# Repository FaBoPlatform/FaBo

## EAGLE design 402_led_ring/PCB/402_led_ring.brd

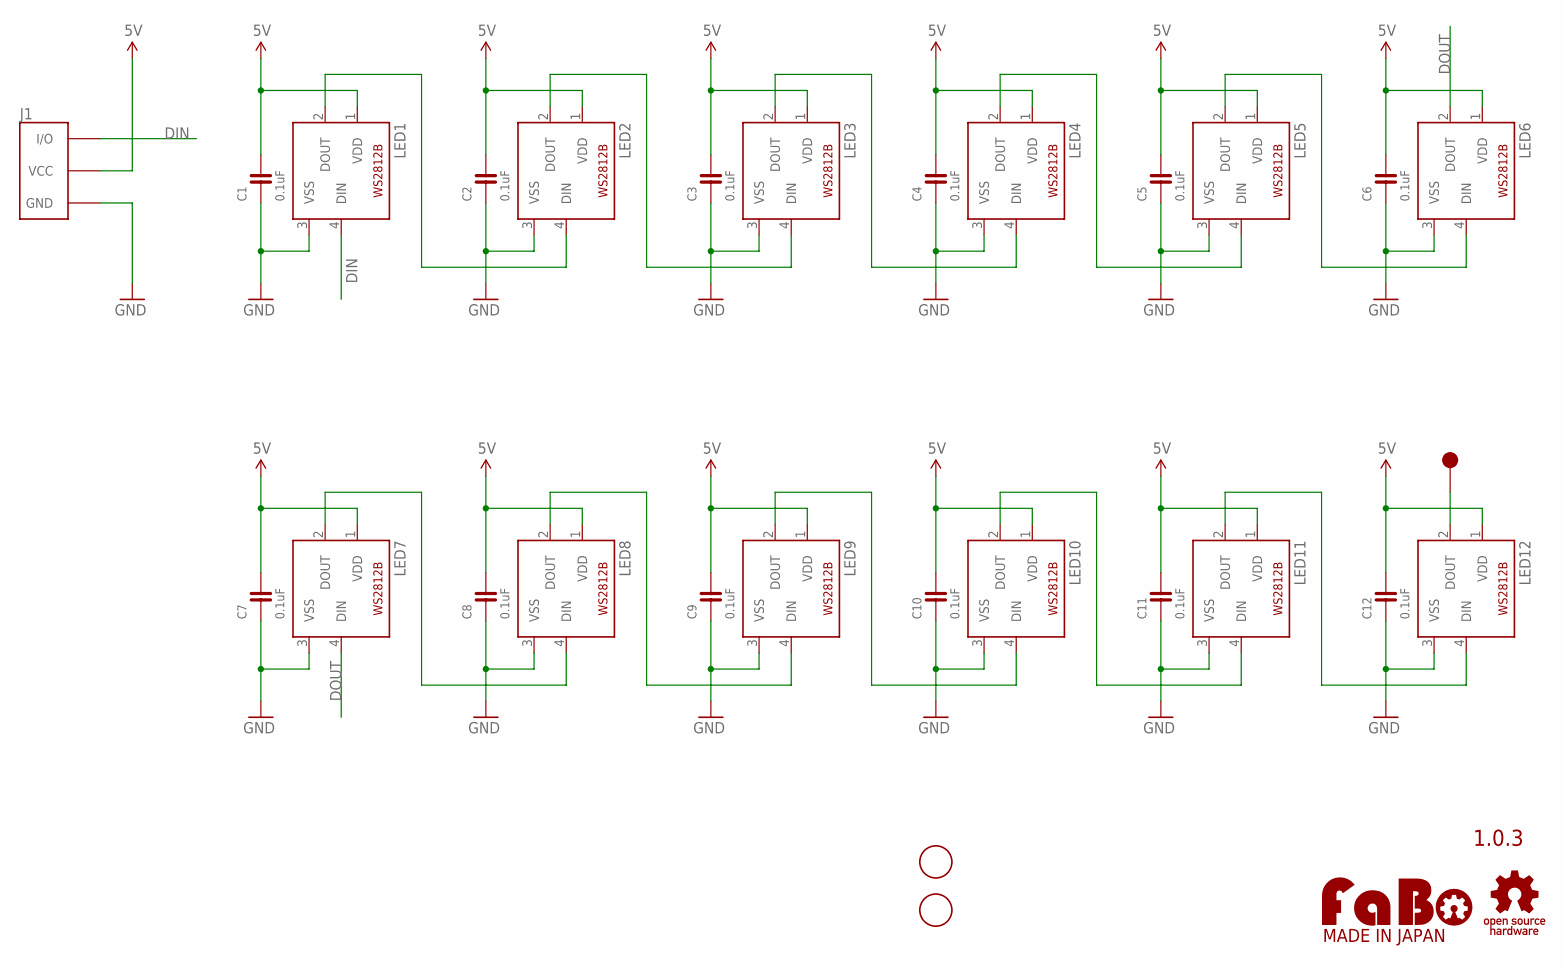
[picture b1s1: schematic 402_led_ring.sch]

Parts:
C1, C2, C3, C4, C5, C6, C7, C8, C9, C10, C11, C12: 0.1uF; 0603
J1: FABO_BRICK_3PIN-S03B-PASK-2_LONG; FABO_BRICK_3PIN_S03B-PASK-2_LONG
LED1, LED2, LED3, LED4, LED5, LED6, LED7, LED8, LED9, LED10, LED11, LED12: WS2812B
TP1: TP-10
U$2, U$3: SCREW-PAD-3MM; SCREWPAD_3MM
U$4: LOGO_OSHW-M_BOTTOM; LOGO_OSHW_M_BOTTOM
U$5: LOGO_FABO-M; LOGO_FABO_MS

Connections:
5V: C1.2, C2.2, C3.2, C4.2, C5.2, C6.2, C7.2, C8.2, C9.2, C10.2, C11.2, C12.2, J1.VCC, LED1.1 (VDD), LED2.1 (VDD), LED3.1 (VDD), LED4.1 (VDD), LED5.1 (VDD), LED6.1 (VDD), LED7.1 (VDD), LED8.1 (VDD), LED9.1 (VDD), LED10.1 (VDD), LED11.1 (VDD), LED12.1 (VDD)
DIN: J1.I/O, LED1.4 (DIN)
DOUT: LED6.2 (DOUT), LED7.4 (DIN)
GND: C1.1, C2.1, C3.1, C4.1, C5.1, C6.1, C7.1, C8.1, C9.1, C10.1, C11.1, C12.1, J1.GND, LED1.3 (VSS), LED2.3 (VSS), LED3.3 (VSS), LED4.3 (VSS), LED5.3 (VSS), LED6.3 (VSS), LED7.3 (VSS), LED8.3 (VSS), LED9.3 (VSS), LED10.3 (VSS), LED11.3 (VSS), LED12.3 (VSS)
unnamed: LED1.2 (DOUT), LED2.4 (DIN)
unnamed: LED2.2 (DOUT), LED3.4 (DIN)
unnamed: LED3.2 (DOUT), LED4.4 (DIN)
unnamed: LED4.2 (DOUT), LED5.4 (DIN)
unnamed: LED5.2 (DOUT), LED6.4 (DIN)
unnamed: LED7.2 (DOUT), LED8.4 (DIN)
unnamed: LED8.2 (DOUT), LED9.4 (DIN)
unnamed: LED9.2 (DOUT), LED10.4 (DIN)
unnamed: LED10.2 (DOUT), LED11.4 (DIN)
unnamed: LED11.2 (DOUT), LED12.4 (DIN)
unnamed: LED12.2 (DOUT), TP1.1

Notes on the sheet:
1.0.3

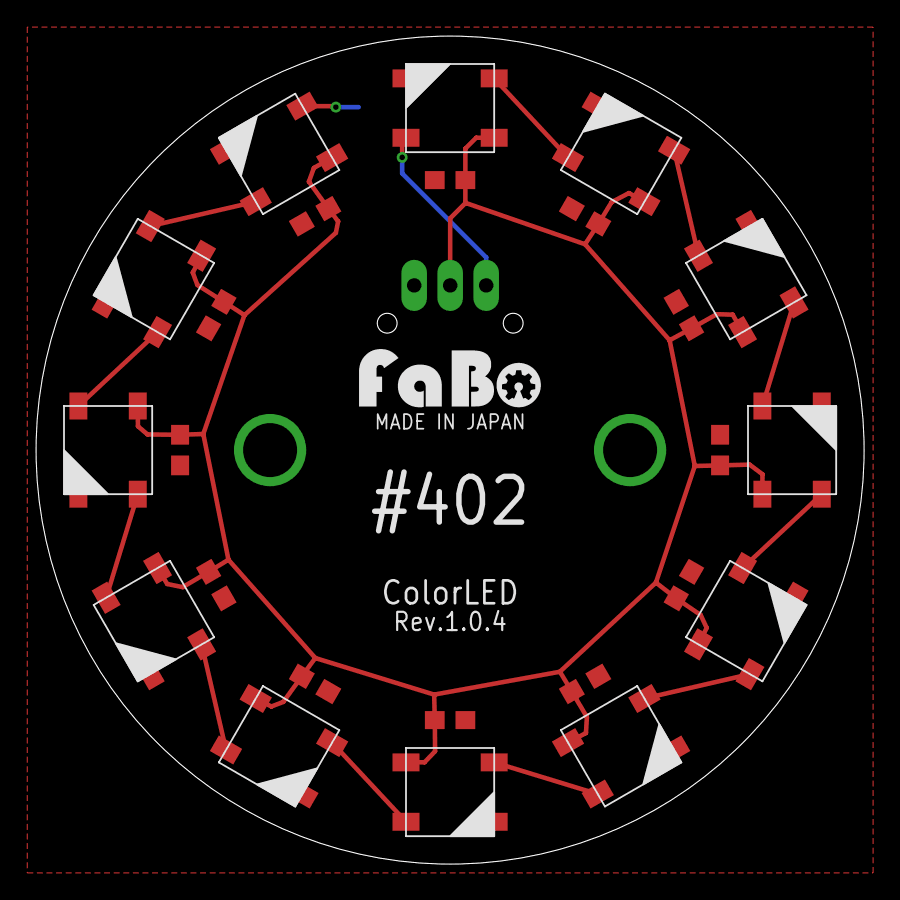
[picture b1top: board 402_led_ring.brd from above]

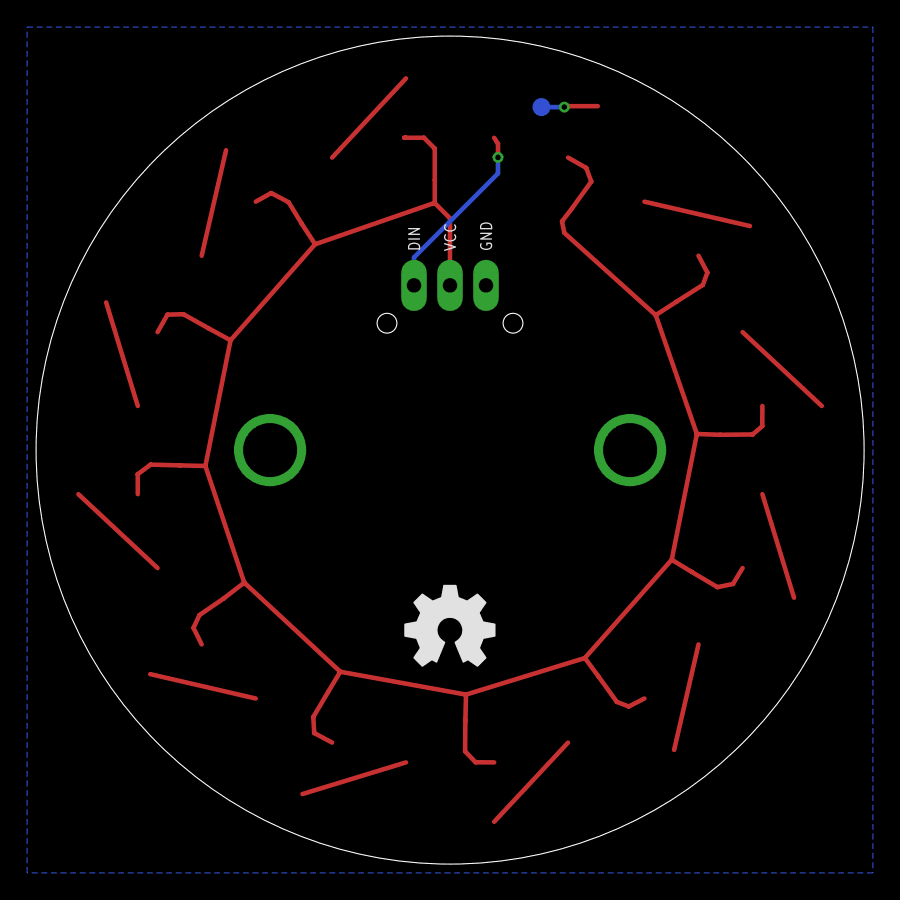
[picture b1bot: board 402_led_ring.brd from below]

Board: 2 copper layers, 46.0 x 46.0 mm, 30 parts (2 on the bottom side), 15 nets.

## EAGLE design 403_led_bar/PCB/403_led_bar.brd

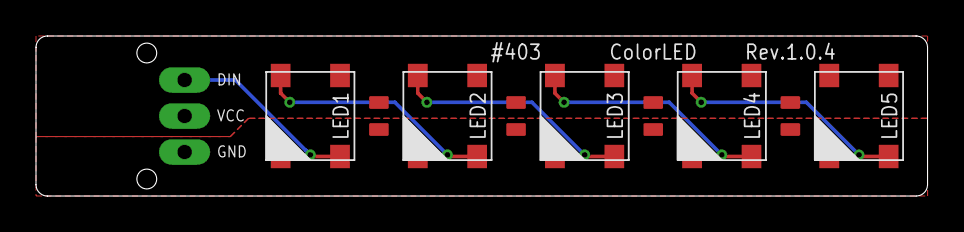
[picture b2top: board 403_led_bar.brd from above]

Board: 2 copper layers, 49.5 x 8.9 mm, 12 parts (0 on the bottom side), 7 nets.

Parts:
C1, C2, C3, C4: 0.1uF; 0603-NARROW
J1: FABO_BRICK_3PIN_S03B-PASK-2_LONG
LED1, LED2, LED3, LED4, LED5: WS2812B_NARROW
U$2: LOGO_OSHW_M_BOTTOM
U$3: LOGO_FABO_MS_BOTTOM

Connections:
5V: C1.2, C2.2, C3.2, C4.2, J1.VCC, LED1.1-VDD, LED2.1-VDD, LED3.1-VDD, LED4.1-VDD, LED5.1-VDD
GND: C1.1, C2.1, C3.1, C4.1, J1.GND, LED1.3-VSS, LED2.3-VSS, LED3.3-VSS, LED4.3-VSS, LED5.3-VSS
IN: J1.I/O, LED1.4-DIN
unnamed: LED1.2-DOUT, LED2.4-DIN
unnamed: LED2.2-DOUT, LED3.4-DIN
unnamed: LED3.2-DOUT, LED4.4-DIN
unnamed: LED4.2-DOUT, LED5.4-DIN

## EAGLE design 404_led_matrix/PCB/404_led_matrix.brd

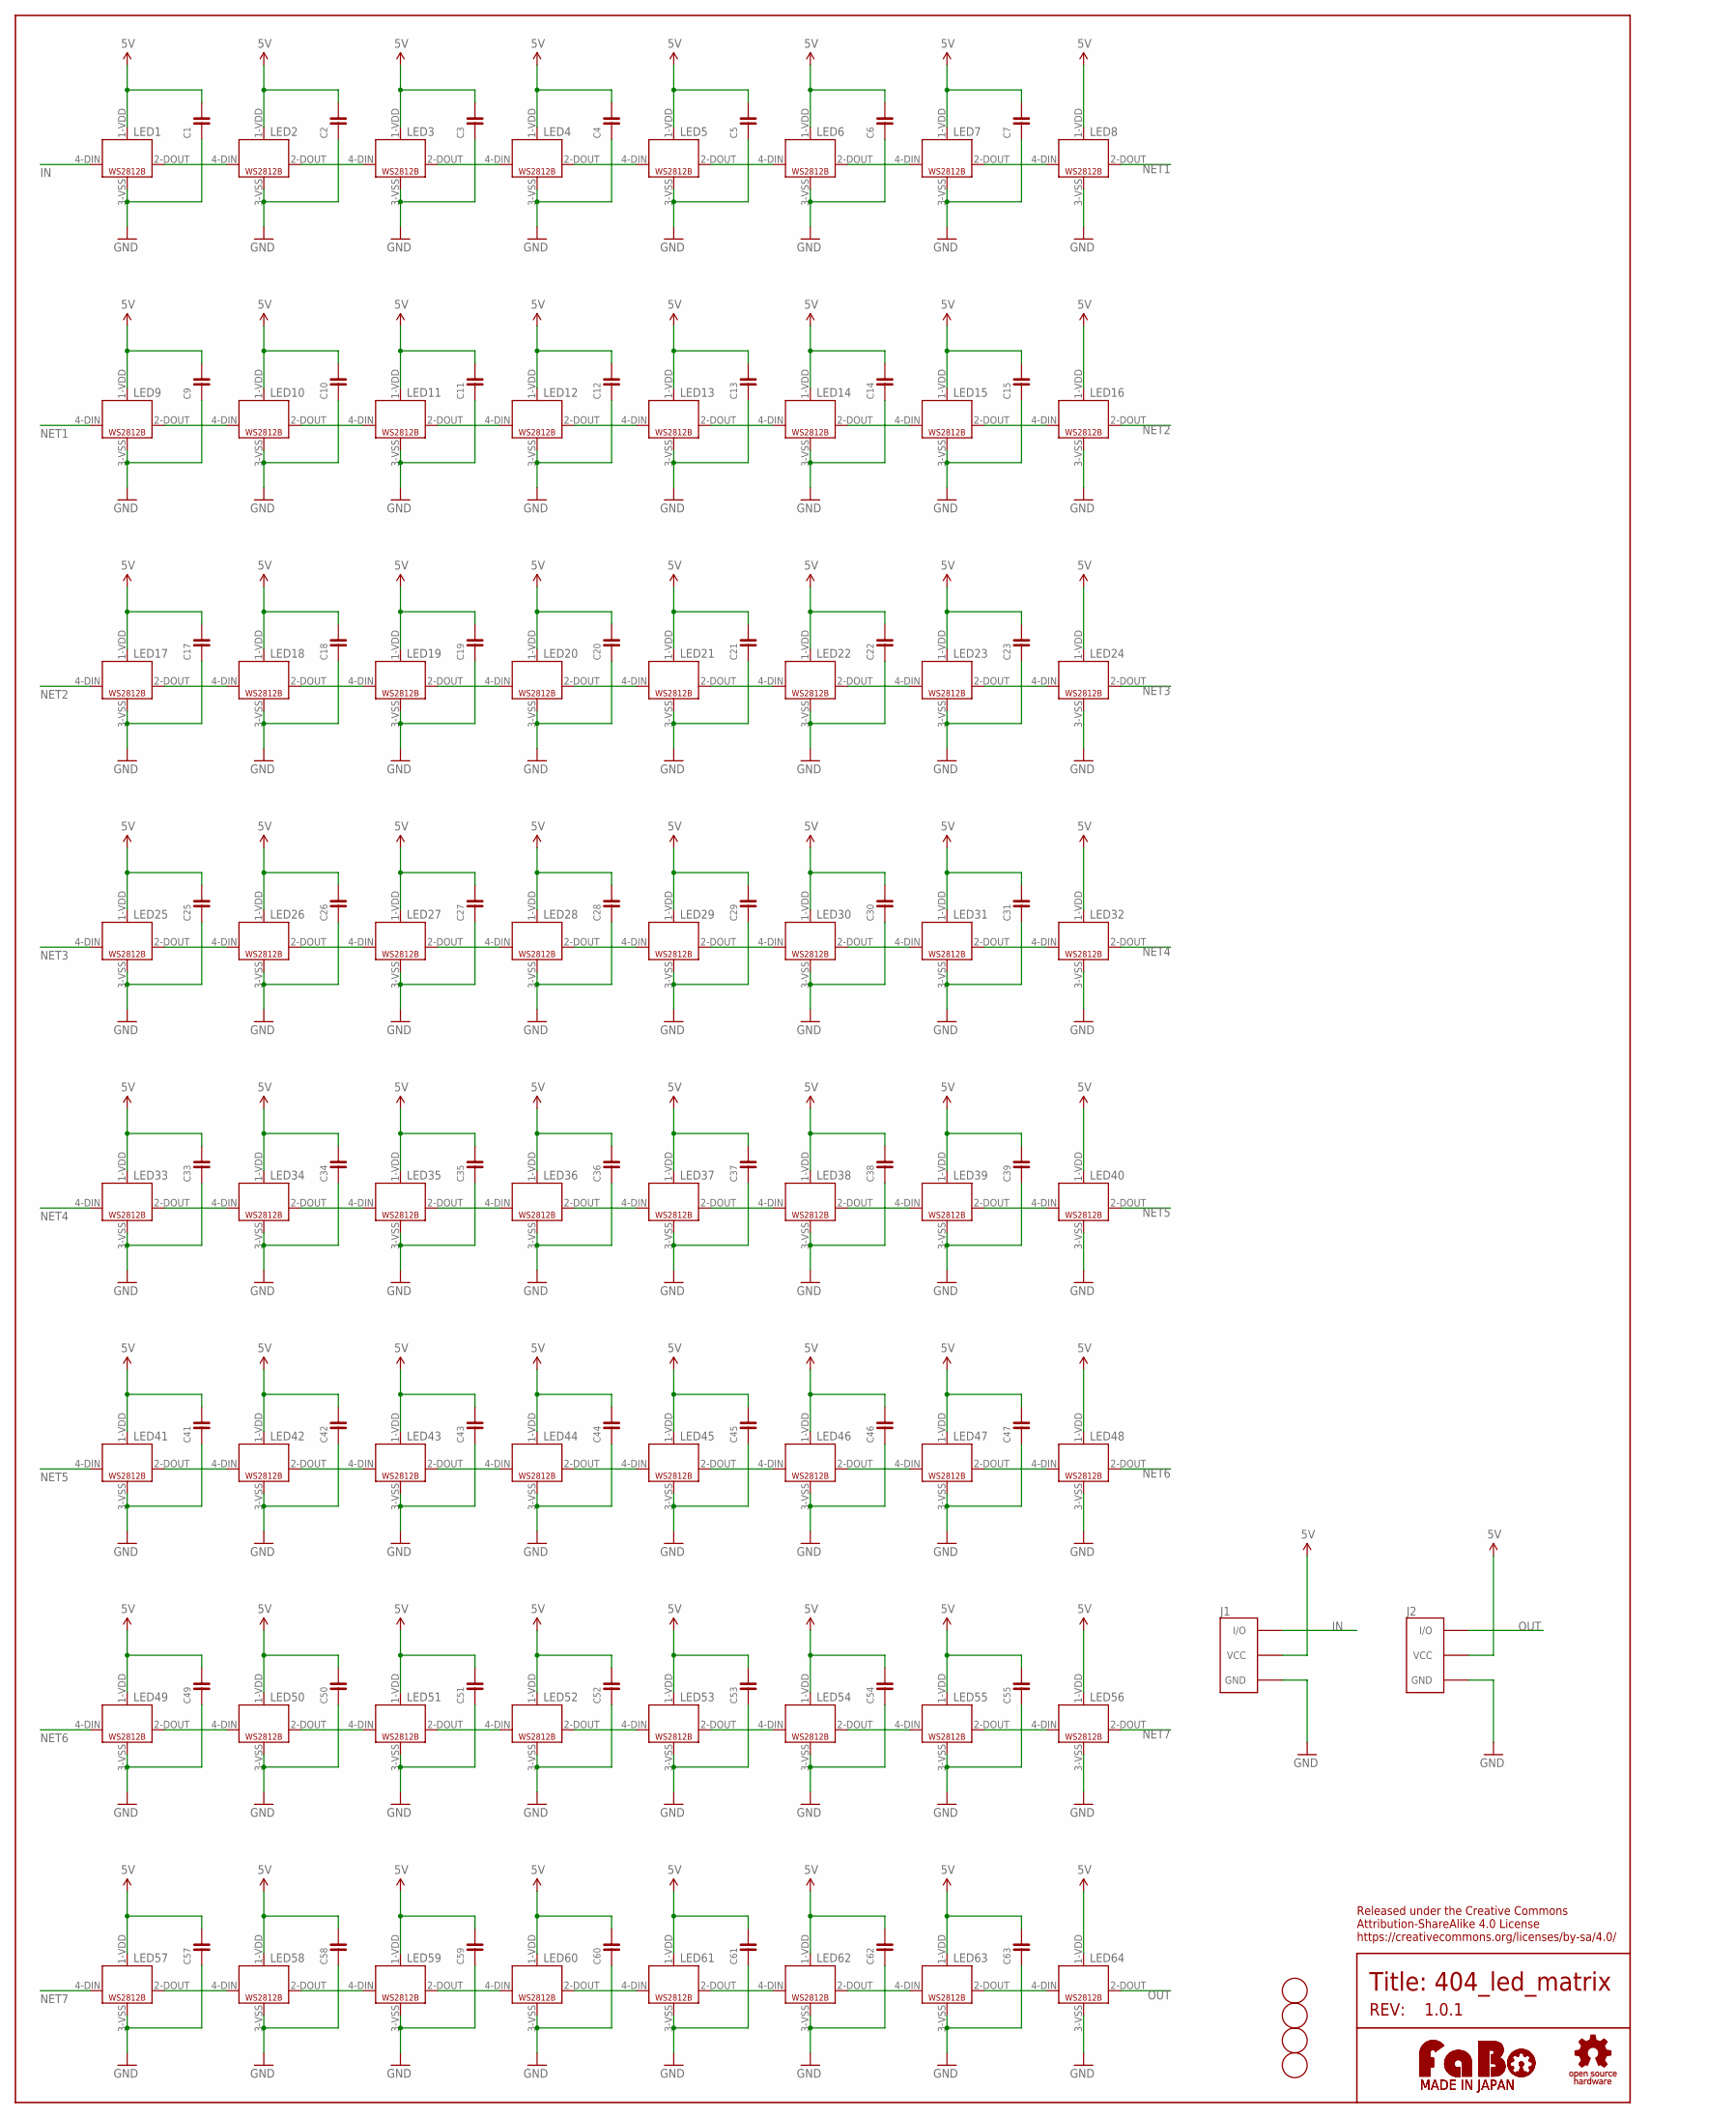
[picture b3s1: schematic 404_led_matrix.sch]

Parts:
C1, C2, C3, C4, C5, C6, C7, C9, C10, C11, C12, C13, C14, C15, C17, C18, C19, C20, C21, C22, C23, C25, C26, C27, C28, C29, C30, C31, C33, C34, C35, C36, C37, C38, C39, C41, C42, C43, C44, C45, C46, C47, C49, C50, C51, C52, C53, C54, C55, C57, C58, C59, C60, C61, C62, C63: CAPACITOR-0603; 0603
HOLE1, HOLE2, HOLE3, HOLE4: SCREW-PAD-2.8MM; SCREWPAD_2.8MM
J1, J2: FABO_BRICK_3PIN-S03B-PASK-2; FABO_BRICK_3PIN_S03B-PASK-2
LED1, LED2, LED3, LED4, LED5, LED6, LED7, LED8, LED9, LED10, LED11, LED12, LED13, LED14, LED15, LED16, LED17, LED18, LED19, LED20, LED21, LED22, LED23, LED24, LED25, LED26, LED27, LED28, LED29, LED30, LED31, LED32, LED33, LED34, LED35, LED36, LED37, LED38, LED39, LED40, LED41, LED42, LED43, LED44, LED45, LED46, LED47, LED48, LED49, LED50, LED51, LED52, LED53, LED54, LED55, LED56, LED57, LED58, LED59, LED60, LED61, LED62, LED63, LED64: WS2812B_NARROW
U$1: LOGO_OSHW-M_BOTTOM; LOGO_OSHW_M_BOTTOM
U$2: LOGO_FABO-L_BOTTOM; LOGO_FABO_L_BOTTOM
U$4: LOGO_FABO-S; LOGO_FABO_S

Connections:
5V: C1.2, C2.2, C3.2, C4.2, C5.2, C6.2, C7.2, C9.2, C10.2, C11.2, C12.2, C13.2, C14.2, C15.2, C17.2, C18.2, C19.2, C20.2, C21.2, C22.2, C23.2, C25.2, C26.2, C27.2, C28.2, C29.2, C30.2, C31.2, C33.2, C34.2, C35.2, C36.2, C37.2, C38.2, C39.2, C41.2, C42.2, C43.2, C44.2, C45.2, C46.2, C47.2, C49.2, C50.2, C51.2, C52.2, C53.2, C54.2, C55.2, C57.2, C58.2, C59.2, C60.2, C61.2, C62.2, C63.2, J1.VCC, J2.VCC, LED1.1-VDD (VDD), LED2.1-VDD (VDD), LED3.1-VDD (VDD), LED4.1-VDD (VDD), LED5.1-VDD (VDD), LED6.1-VDD (VDD), LED7.1-VDD (VDD), LED8.1-VDD (VDD), LED9.1-VDD (VDD), LED10.1-VDD (VDD), LED11.1-VDD (VDD), LED12.1-VDD (VDD), LED13.1-VDD (VDD), LED14.1-VDD (VDD), LED15.1-VDD (VDD), LED16.1-VDD (VDD), LED17.1-VDD (VDD), LED18.1-VDD (VDD), LED19.1-VDD (VDD), LED20.1-VDD (VDD), LED21.1-VDD (VDD), LED22.1-VDD (VDD), LED23.1-VDD (VDD), LED24.1-VDD (VDD), LED25.1-VDD (VDD), LED26.1-VDD (VDD), LED27.1-VDD (VDD), LED28.1-VDD (VDD), LED29.1-VDD (VDD), LED30.1-VDD (VDD), LED31.1-VDD (VDD), LED32.1-VDD (VDD), LED33.1-VDD (VDD)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
GND: C1.1, C2.1, C3.1, C4.1, C5.1, C6.1, C7.1, C9.1, C10.1, C11.1, C12.1, C13.1, C14.1, C15.1, C17.1, C18.1, C19.1, C20.1, C21.1, C22.1, C23.1, C25.1, C26.1, C27.1, C28.1, C29.1, C30.1, C31.1, C33.1, C34.1, C35.1, C36.1, C37.1, C38.1, C39.1, C41.1, C42.1, C43.1, C44.1, C45.1, C46.1, C47.1, C49.1, C50.1, C51.1, C52.1, C53.1, C54.1, C55.1, C57.1, C58.1, C59.1, C60.1, C61.1, C62.1, C63.1, J1.GND, J2.GND, LED1.3-VSS (VSS), LED2.3-VSS (VSS), LED3.3-VSS (VSS), LED4.3-VSS (VSS), LED5.3-VSS (VSS), LED6.3-VSS (VSS), LED7.3-VSS (VSS), LED8.3-VSS (VSS), LED9.3-VSS (VSS), LED10.3-VSS (VSS), LED11.3-VSS (VSS), LED12.3-VSS (VSS), LED13.3-VSS (VSS), LED14.3-VSS (VSS), LED15.3-VSS (VSS), LED16.3-VSS (VSS), LED17.3-VSS (VSS), LED18.3-VSS (VSS), LED19.3-VSS (VSS), LED20.3-VSS (VSS), LED21.3-VSS (VSS), LED22.3-VSS (VSS), LED23.3-VSS (VSS), LED24.3-VSS (VSS), LED25.3-VSS (VSS), LED26.3-VSS (VSS), LED27.3-VSS (VSS), LED28.3-VSS (VSS), LED29.3-VSS (VSS), LED30.3-VSS (VSS), LED31.3-VSS (VSS), LED32.3-VSS (VSS), LED33.3-VSS (VSS)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
IN: J1.I/O, LED1.4-DIN (DIN)
unnamed: LED3.2-DOUT (DOUT), LED4.4-DIN (DIN)
unnamed: LED4.2-DOUT (DOUT), LED5.4-DIN (DIN)
unnamed: LED5.2-DOUT (DOUT), LED6.4-DIN (DIN)
unnamed: LED6.2-DOUT (DOUT), LED7.4-DIN (DIN)
unnamed: LED1.2-DOUT (DOUT), LED2.4-DIN (DIN)
unnamed: LED7.2-DOUT (DOUT), LED8.4-DIN (DIN)
unnamed: LED9.2-DOUT (DOUT), LED10.4-DIN (DIN)
unnamed: LED10.2-DOUT (DOUT), LED11.4-DIN (DIN)
unnamed: LED11.2-DOUT (DOUT), LED12.4-DIN (DIN)
unnamed: LED12.2-DOUT (DOUT), LED13.4-DIN (DIN)
unnamed: LED13.2-DOUT (DOUT), LED14.4-DIN (DIN)
unnamed: LED14.2-DOUT (DOUT), LED15.4-DIN (DIN)
unnamed: LED15.2-DOUT (DOUT), LED16.4-DIN (DIN)
unnamed: LED17.2-DOUT (DOUT), LED18.4-DIN (DIN)
unnamed: LED18.2-DOUT (DOUT), LED19.4-DIN (DIN)
unnamed: LED19.2-DOUT (DOUT), LED20.4-DIN (DIN)
unnamed: LED20.2-DOUT (DOUT), LED21.4-DIN (DIN)
unnamed: LED21.2-DOUT (DOUT), LED22.4-DIN (DIN)
unnamed: LED22.2-DOUT (DOUT), LED23.4-DIN (DIN)
unnamed: LED23.2-DOUT (DOUT), LED24.4-DIN (DIN)
unnamed: LED25.2-DOUT (DOUT), LED26.4-DIN (DIN)
unnamed: LED26.2-DOUT (DOUT), LED27.4-DIN (DIN)
unnamed: LED27.2-DOUT (DOUT), LED28.4-DIN (DIN)
unnamed: LED28.2-DOUT (DOUT), LED29.4-DIN (DIN)
unnamed: LED29.2-DOUT (DOUT), LED30.4-DIN (DIN)
unnamed: LED30.2-DOUT (DOUT), LED31.4-DIN (DIN)
unnamed: LED31.2-DOUT (DOUT), LED32.4-DIN (DIN)
unnamed: LED33.2-DOUT (DOUT), LED34.4-DIN (DIN)
unnamed: LED34.2-DOUT (DOUT), LED35.4-DIN (DIN)
unnamed: LED35.2-DOUT (DOUT), LED36.4-DIN (DIN)
unnamed: LED36.2-DOUT (DOUT), LED37.4-DIN (DIN)
unnamed: LED37.2-DOUT (DOUT), LED38.4-DIN (DIN)
unnamed: LED38.2-DOUT (DOUT), LED39.4-DIN (DIN)
unnamed: LED39.2-DOUT (DOUT), LED40.4-DIN (DIN)
unnamed: LED41.2-DOUT (DOUT), LED42.4-DIN (DIN)
unnamed: LED42.2-DOUT (DOUT), LED43.4-DIN (DIN)
unnamed: LED43.2-DOUT (DOUT), LED44.4-DIN (DIN)
unnamed: LED44.2-DOUT (DOUT), LED45.4-DIN (DIN)
unnamed: LED45.2-DOUT (DOUT), LED46.4-DIN (DIN)
unnamed: LED46.2-DOUT (DOUT), LED47.4-DIN (DIN)
unnamed: LED47.2-DOUT (DOUT), LED48.4-DIN (DIN)
unnamed: LED49.2-DOUT (DOUT), LED50.4-DIN (DIN)
unnamed: LED50.2-DOUT (DOUT), LED51.4-DIN (DIN)
unnamed: LED51.2-DOUT (DOUT), LED52.4-DIN (DIN)
unnamed: LED52.2-DOUT (DOUT), LED53.4-DIN (DIN)
unnamed: LED53.2-DOUT (DOUT), LED54.4-DIN (DIN)
unnamed: LED54.2-DOUT (DOUT), LED55.4-DIN (DIN)
unnamed: LED55.2-DOUT (DOUT), LED56.4-DIN (DIN)
unnamed: LED57.2-DOUT (DOUT), LED58.4-DIN (DIN)
unnamed: LED58.2-DOUT (DOUT), LED59.4-DIN (DIN)
unnamed: LED59.2-DOUT (DOUT), LED60.4-DIN (DIN)
unnamed: LED60.2-DOUT (DOUT), LED61.4-DIN (DIN)
unnamed: LED61.2-DOUT (DOUT), LED62.4-DIN (DIN)
unnamed: LED62.2-DOUT (DOUT), LED63.4-DIN (DIN)
unnamed: LED63.2-DOUT (DOUT), LED64.4-DIN (DIN)
unnamed: LED2.2-DOUT (DOUT), LED3.4-DIN (DIN)
NET1: LED8.2-DOUT (DOUT), LED9.4-DIN (DIN)
NET2: LED16.2-DOUT (DOUT), LED17.4-DIN (DIN)
NET3: LED24.2-DOUT (DOUT), LED25.4-DIN (DIN)
NET4: LED32.2-DOUT (DOUT), LED33.4-DIN (DIN)
NET5: LED40.2-DOUT (DOUT), LED41.4-DIN (DIN)
NET6: LED48.2-DOUT (DOUT), LED49.4-DIN (DIN)
NET7: LED56.2-DOUT (DOUT), LED57.4-DIN (DIN)
OUT: J2.I/O, LED64.2-DOUT (DOUT)

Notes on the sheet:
1.0.1
Title: 404_led_matrix
REV:
Released under the Creative Commons Attribution-ShareAlike 4.0 License https://creativecommons.org/licenses/by-sa/4.0/

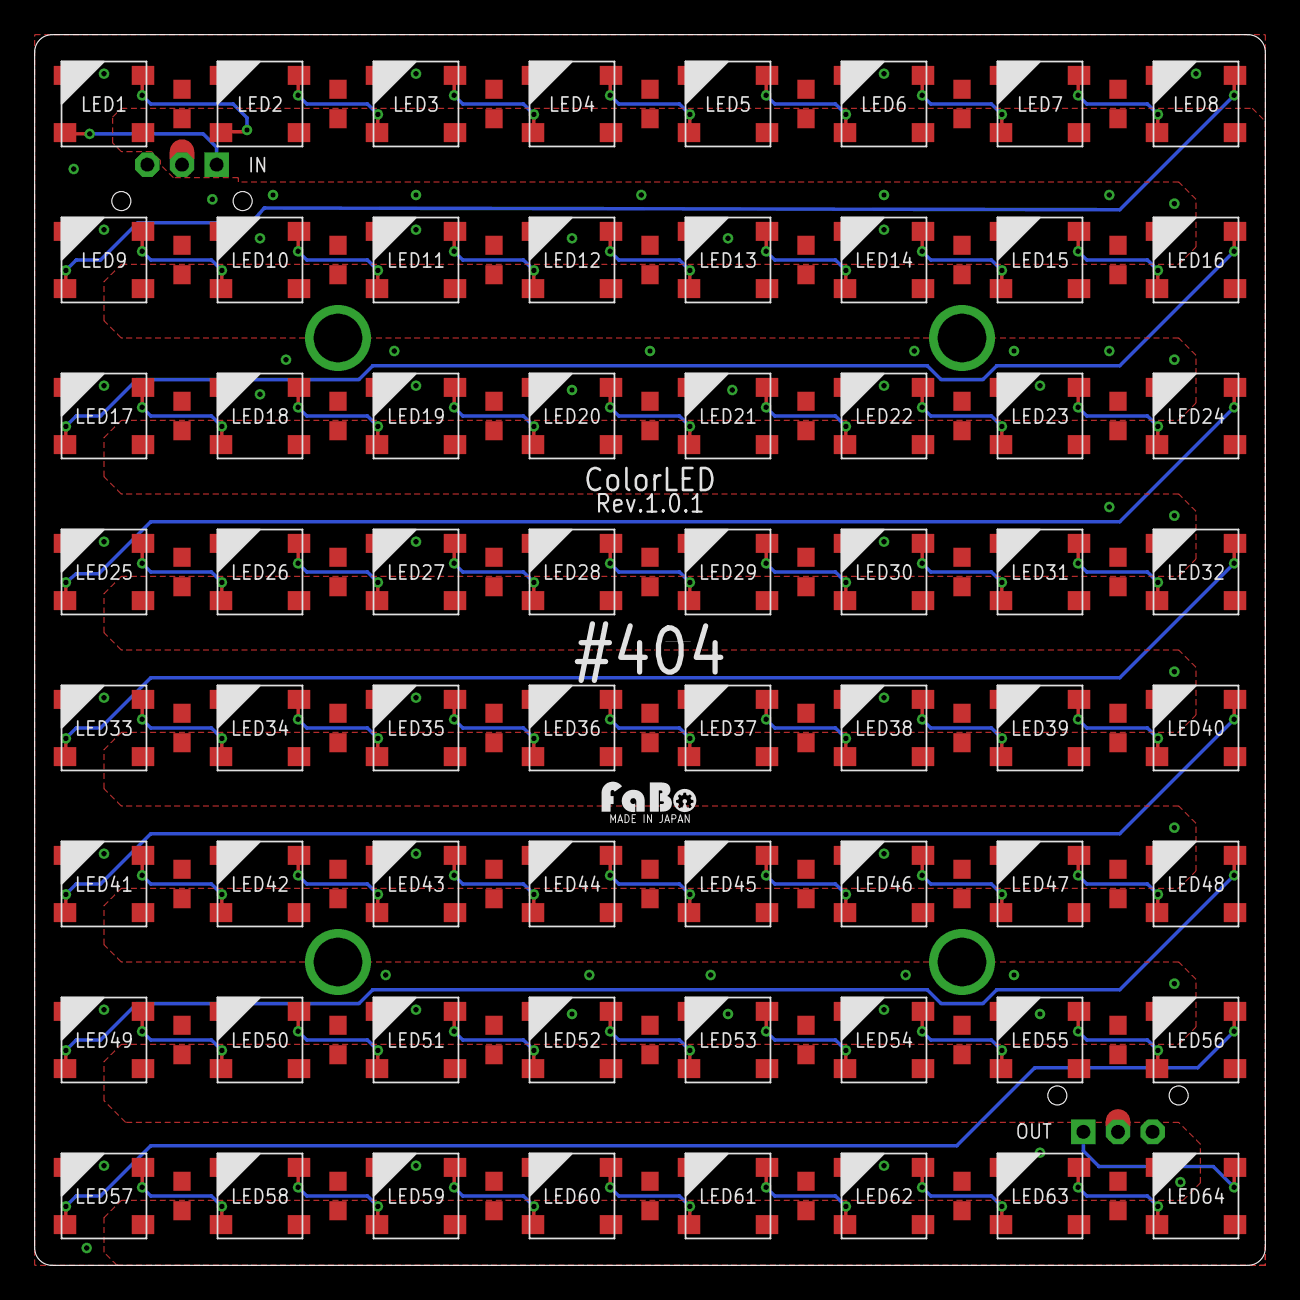
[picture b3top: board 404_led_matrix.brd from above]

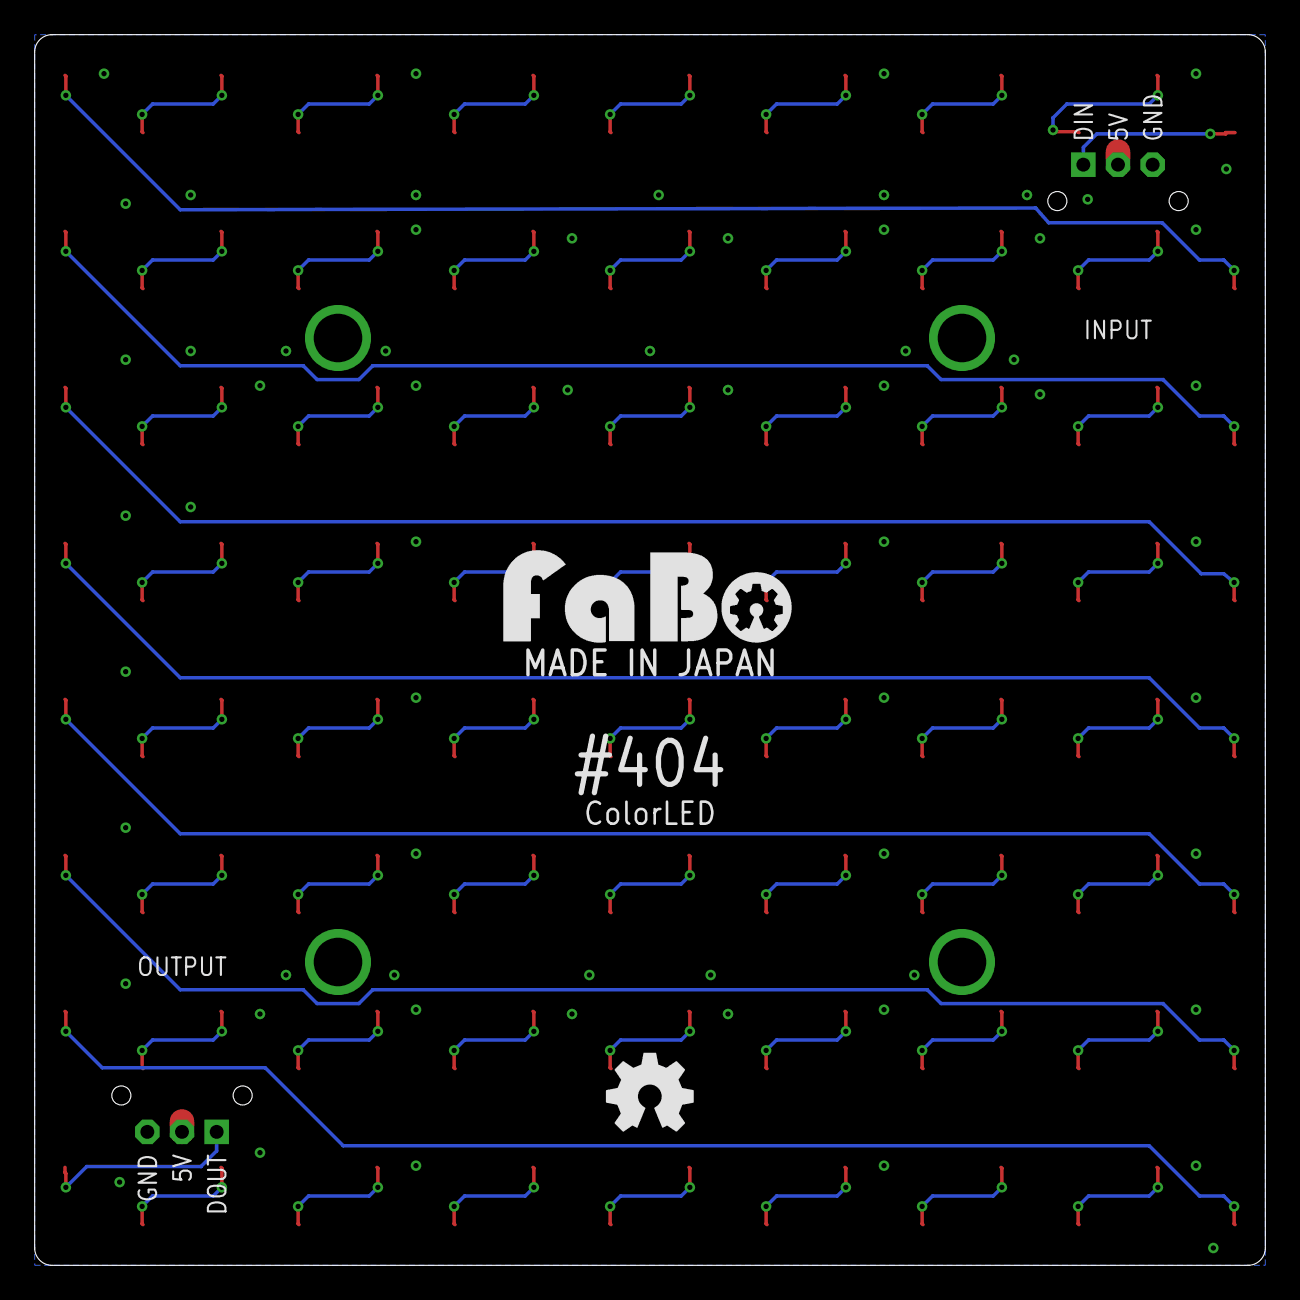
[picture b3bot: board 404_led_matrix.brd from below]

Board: 2 copper layers, 71.0 x 71.0 mm, 129 parts (2 on the bottom side), 67 nets.

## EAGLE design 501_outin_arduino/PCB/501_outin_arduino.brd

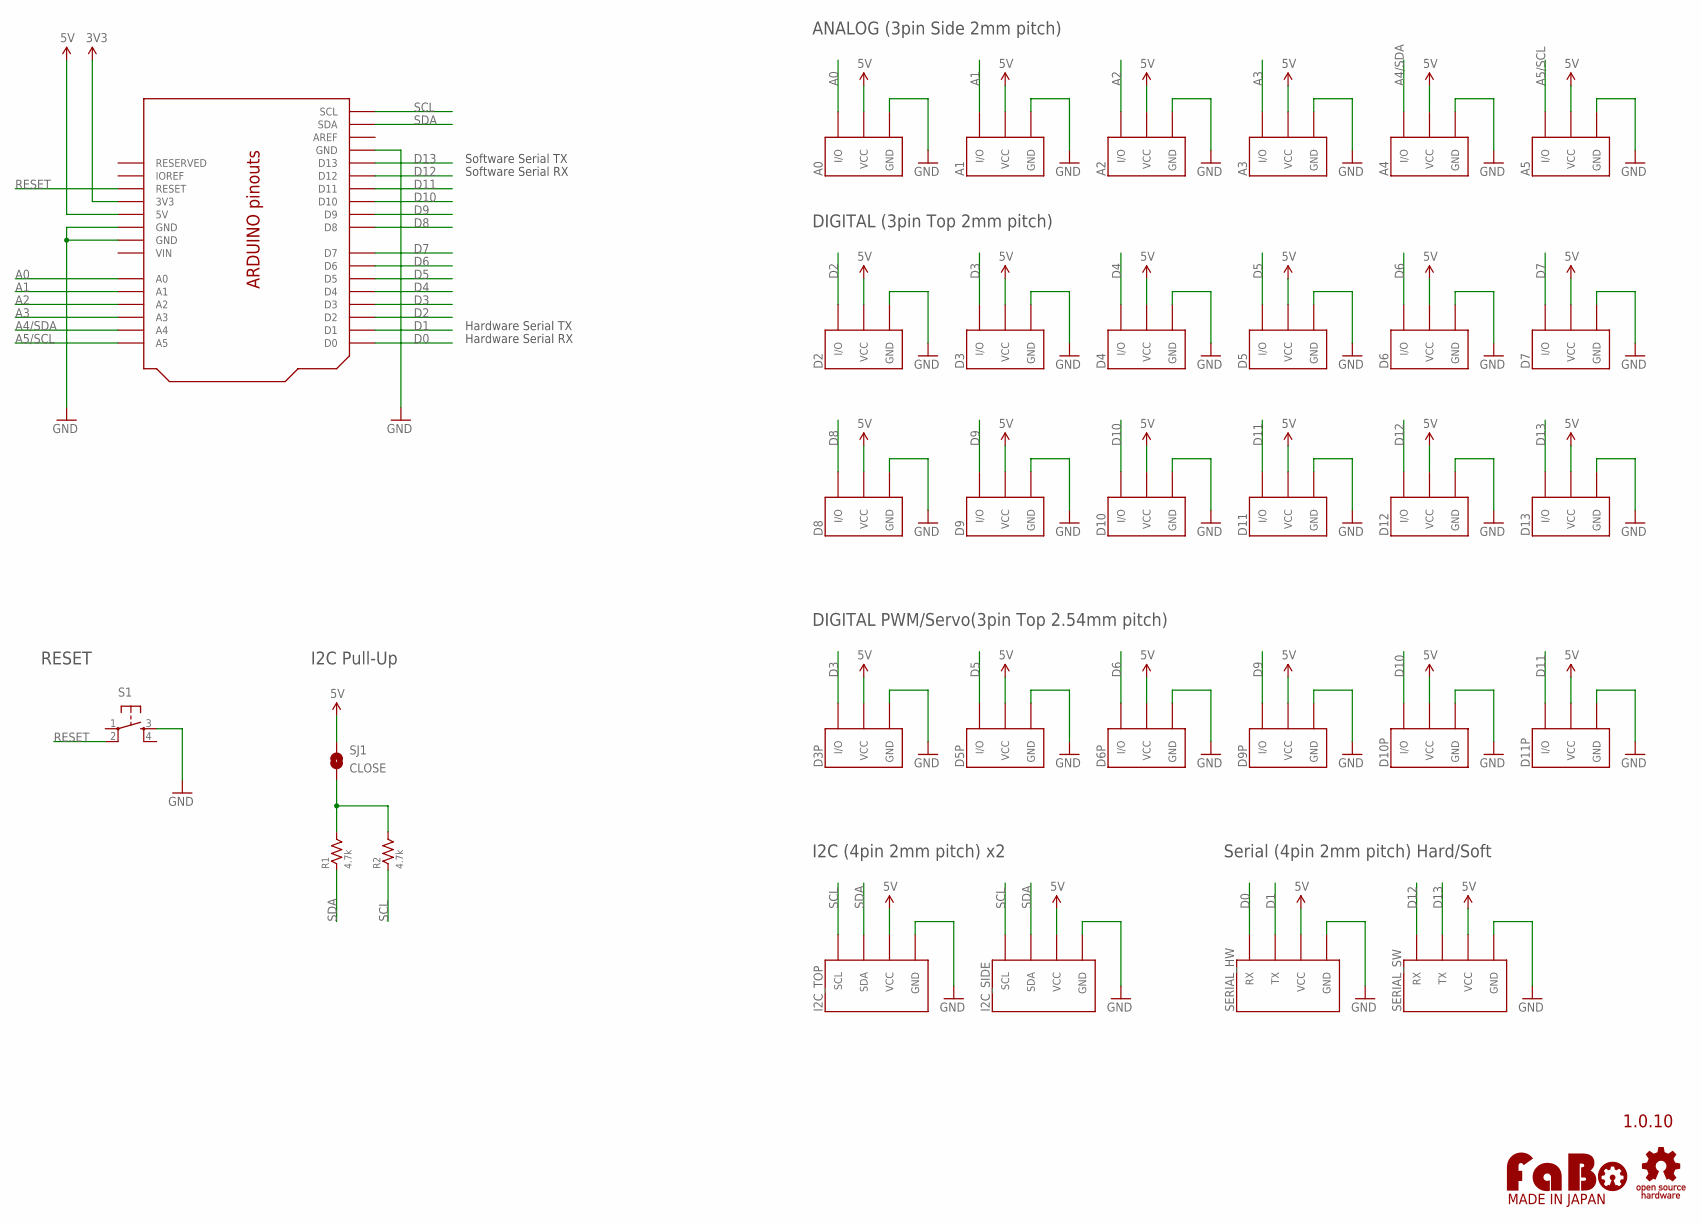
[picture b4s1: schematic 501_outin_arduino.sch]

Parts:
A0, A1, A2, A3, A4, A5: FABO_BRICK_3PIN-S03B-PASK-2_LONG; FABO_BRICK_3PIN_S03B-PASK-2_LONG
D2, D3, D4, D5, D6, D7, D8, D9, D10, D11, D12, D13: FABO_BRICK_3PIN-B03B-PASK-1; FABO_BRICK_3PIN_B03B-PASK-1
D3P, D5P, D6P, D9P, D10P, D11P: FABO_BRICK_3PIN-HEADER; FABO_BRICK_3PIN_HEADER
I2C_SIDE: FABO_BRICK_I2C-S04B-PASK-2_LONG; FABO_BRICK_I2C_S04B-PASK-2_LONG
I2C_TOP: FABO_BRICK_I2C-B04B-PASK-1; FABO_BRICK_I2C_B04B-PASK-1
R1, R2: 4.7k; 0603
S1: TACT-SWITCH-6MM; DTS_6_V
SERIAL_HW: FABO_BRICK_SERIAL-B04B-PASK-1; FABO_BRICK_SERIAL_B04B-PASK-1
SERIAL_SW: FABO_BRICK_SERIAL-S04B-PASK-2_LONG; FABO_BRICK_SERIAL_S04B-PASK-2_LONG
SJ1: CLOSE; SMD-JUMPER-2-CLOSE
U1: ARDUINO_UNO_R3_SHIELD-OUTIN; ARDUINO_SHIELD_OUTIN
U$10: LOGO_FABO-M; LOGO_FABO_MS
U$13: LOGO_OSHW-T_M_BOTTOM; LOGO_OSHW_T_MS_BOTTOM

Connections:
3V3: U1.3V3
5V: A0.VCC, A1.VCC, A2.VCC, A3.VCC, A4.VCC, A5.VCC, D2.VCC, D3.VCC, D3P.VCC, D4.VCC, D5.VCC, D5P.VCC, D6.VCC, D6P.VCC, D7.VCC, D8.VCC, D9.VCC, D9P.VCC, D10.VCC, D10P.VCC, D11.VCC, D11P.VCC, D12.VCC, D13.VCC, I2C_SIDE.VCC, I2C_TOP.VCC, SERIAL_HW.VCC, SERIAL_SW.VCC, SJ1.1, U1.5V
A0: A0.I/O, U1.A0
A1: A1.I/O, U1.A1
A2: A2.I/O, U1.A2
A3: A3.I/O, U1.A3
A4/SDA: A4.I/O, U1.A4
A5/SCL: A5.I/O, U1.A5
D0: SERIAL_HW.RX, U1.D0
D1: SERIAL_HW.TX, U1.D1
D2: D2.I/O, U1.D2
D3: D3.I/O, D3P.I/O, U1.D3
D4: D4.I/O, U1.D4
D5: D5.I/O, D5P.I/O, U1.D5
D6: D6.I/O, D6P.I/O, U1.D6
D7: D7.I/O, U1.D7
D8: D8.I/O, U1.D8
D9: D9.I/O, D9P.I/O, U1.D9
D10: D10.I/O, D10P.I/O, U1.D10
D11: D11.I/O, D11P.I/O, U1.D11
D12: D12.I/O, SERIAL_SW.RX, U1.D12
D13: D13.I/O, SERIAL_SW.TX, U1.D13
GND: A0.GND, A1.GND, A2.GND, A3.GND, A4.GND, A5.GND, D2.GND, D3.GND, D3P.GND, D4.GND, D5.GND, D5P.GND, D6.GND, D6P.GND, D7.GND, D8.GND, D9.GND, D9P.GND, D10.GND, D10P.GND, D11.GND, D11P.GND, D12.GND, D13.GND, I2C_SIDE.GND, I2C_TOP.GND, S1.3, SERIAL_HW.GND, SERIAL_SW.GND, U1.GND1 (GND), U1.GND2 (GND), U1.GND3 (GND)
unnamed: R1.2, R2.2, SJ1.2
RESET: S1.2, U1.RESET
SCL: I2C_SIDE.SCL, I2C_TOP.SCL, R2.1, U1.SCL
SDA: I2C_SIDE.SDA, I2C_TOP.SDA, R1.1, U1.SDA
VIN: U1.VIN

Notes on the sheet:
1.0.10
DIGITAL (3pin Top 2mm pitch)
ANALOG (3pin Side 2mm pitch)
DIGITAL PWM/Servo(3pin Top 2.54mm pitch)
I2C (4pin 2mm pitch) x2
Software Serial RX
Software Serial TX
Serial (4pin 2mm pitch) Hard/Soft
Hardware Serial TX
Hardware Serial RX
I2C Pull-Up
RESET

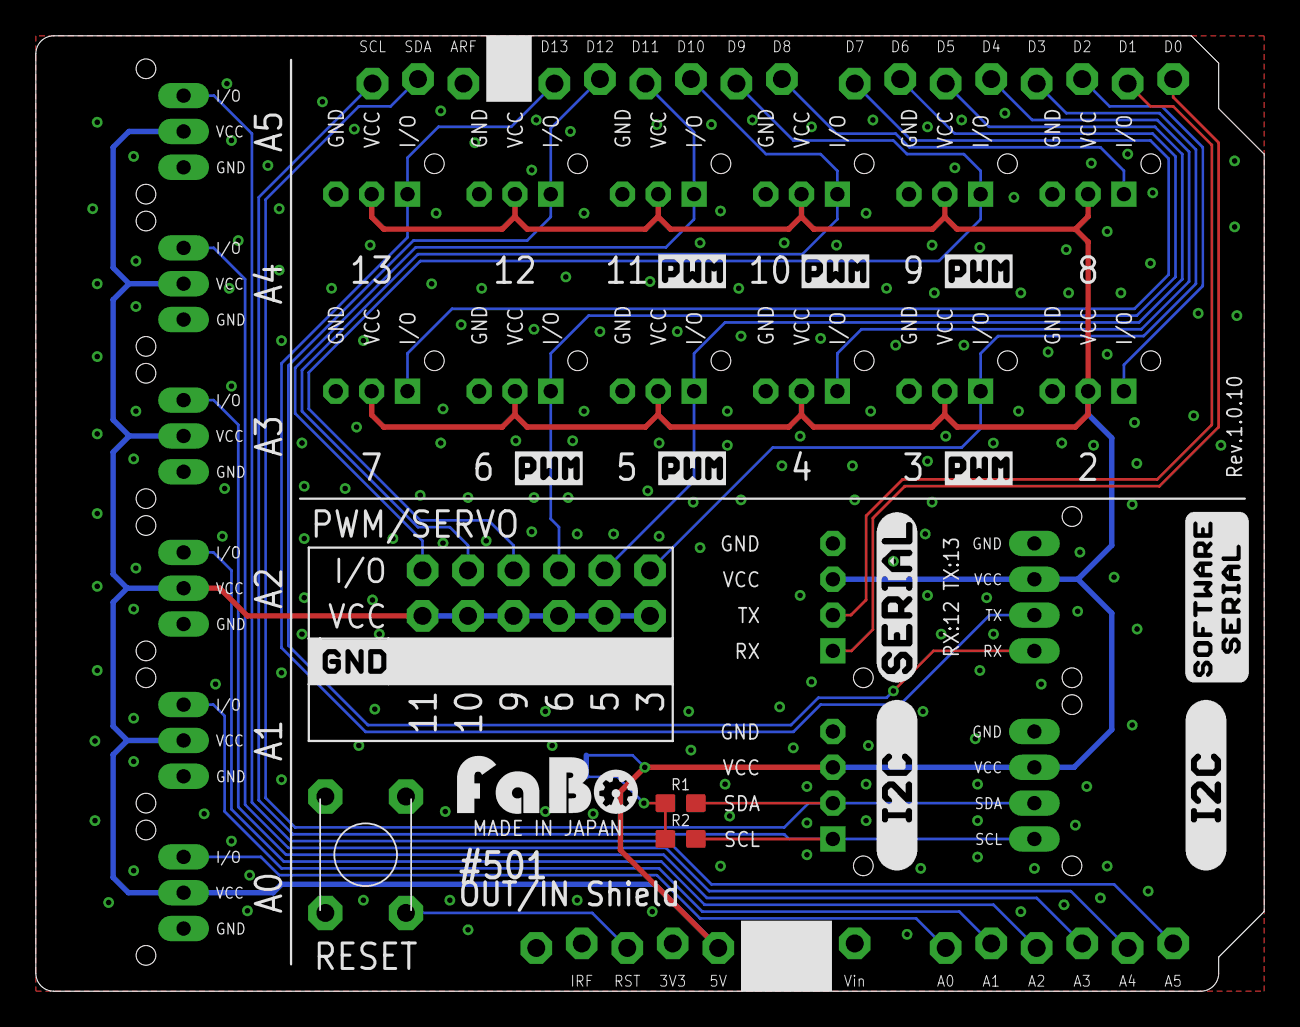
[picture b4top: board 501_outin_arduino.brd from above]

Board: 2 copper layers, 68.6 x 53.3 mm, 47 parts (1 on the bottom side), 26 nets.

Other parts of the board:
U$2: LOGO_SILK_SERIAL2
U$3: LOGO_SILK_SERIAL
U$4, U$5, U$6, U$7, U$8, U$9: LOGO_SILK_PWM
U$11, U$12: LOGO_SILK_I2C
U$14: LOGO_FABO_MS_BOTTOM
U$19: LOGO_SILK_GND

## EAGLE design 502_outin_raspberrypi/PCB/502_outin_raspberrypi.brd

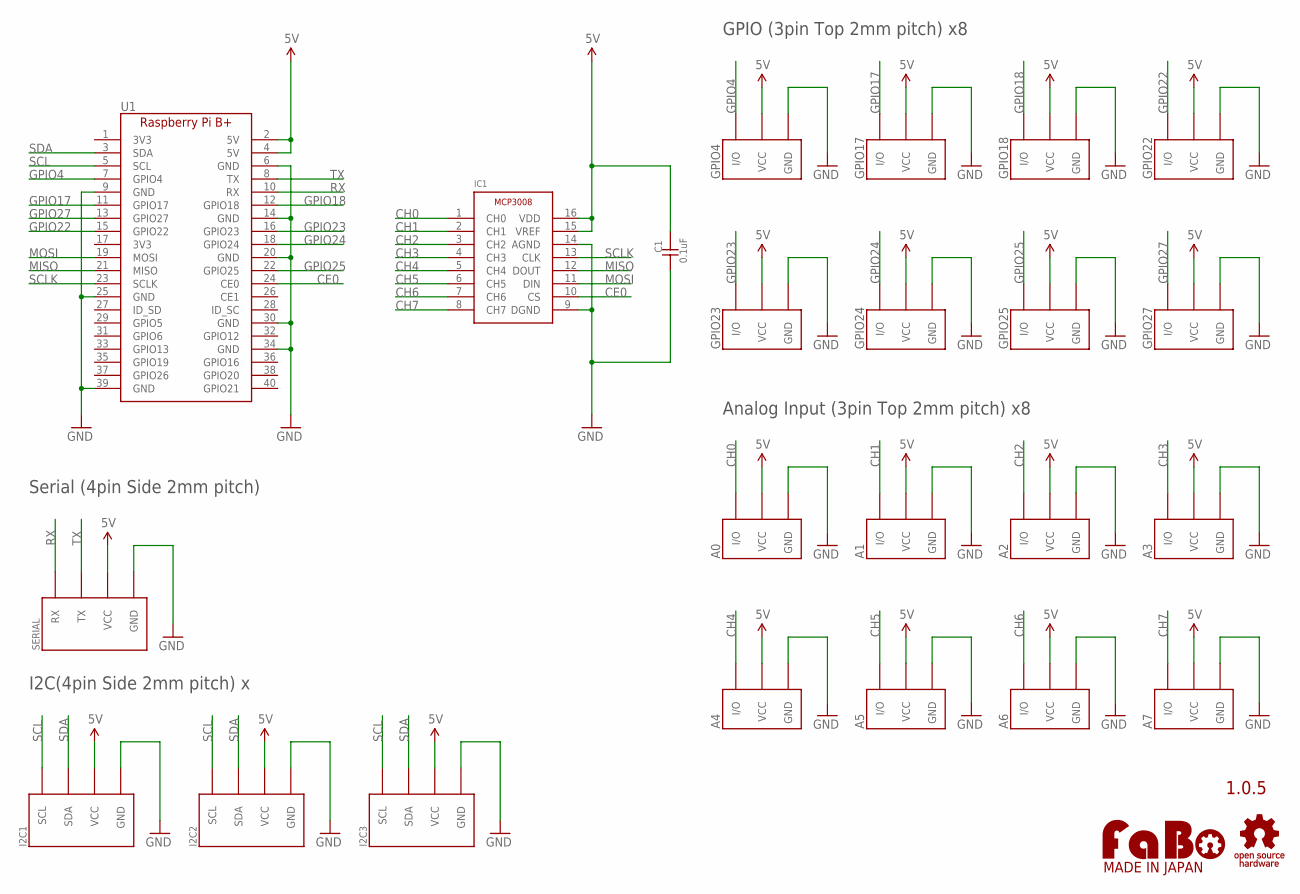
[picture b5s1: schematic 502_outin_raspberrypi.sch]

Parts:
A0, A1, A2, A3, A4, A5, A6, A7: FABO_BRICK_3PIN-B03B-PASK-1; FABO_BRICK_3PIN_B03B-PASK-1
C1: 0.1uF; 0603
GPIO4, GPIO17, GPIO18, GPIO22, GPIO23, GPIO24, GPIO25, GPIO27: FABO_BRICK_3PIN-B03B-PASK-1; FABO_BRICK_3PIN_B03B-PASK-1
I2C1, I2C2, I2C3: FABO_BRICK_I2C-S04B-PASK-2; FABO_BRICK_I2C_S04B-PASK-2
IC1: MICROCHIP-MCP3008
SERIAL: FABO_BRICK_SERIAL-S04B-PASK-2; FABO_BRICK_SERIAL_S04B-PASK-2
U1: RASPBERRY_PI_B+
U$4: LOGO_OSHW-T_M; LOGO_OSHW_T_MS
U$14: LOGO_FABO-M; LOGO_FABO_MS

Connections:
5V: A0.VCC, A1.VCC, A2.VCC, A3.VCC, A4.VCC, A5.VCC, A6.VCC, A7.VCC, C1.2, GPIO4.VCC, GPIO17.VCC, GPIO18.VCC, GPIO22.VCC, GPIO23.VCC, GPIO24.VCC, GPIO25.VCC, GPIO27.VCC, I2C1.VCC, I2C2.VCC, I2C3.VCC, IC1.15 (VREF), IC1.16 (VDD), SERIAL.VCC, U1.2 (5V), U1.4 (5V)
CE0: IC1.10 (CS), U1.24 (CE0)
CH0: A0.I/O, IC1.1 (CH0)
CH1: A1.I/O, IC1.2 (CH1)
CH2: A2.I/O, IC1.3 (CH2)
CH3: A3.I/O, IC1.4 (CH3)
CH4: A4.I/O, IC1.5 (CH4)
CH5: A5.I/O, IC1.6 (CH5)
CH6: A6.I/O, IC1.7 (CH6)
CH7: A7.I/O, IC1.8 (CH7)
GND: A0.GND, A1.GND, A2.GND, A3.GND, A4.GND, A5.GND, A6.GND, A7.GND, C1.1, GPIO4.GND, GPIO17.GND, GPIO18.GND, GPIO22.GND, GPIO23.GND, GPIO24.GND, GPIO25.GND, GPIO27.GND, I2C1.GND, I2C2.GND, I2C3.GND, IC1.9 (DGND), IC1.14 (AGND), SERIAL.GND, U1.6 (GND), U1.9 (GND), U1.14 (GND), U1.20 (GND), U1.25 (GND), U1.30 (GND), U1.34 (GND), U1.39 (GND)
GPIO4: GPIO4.I/O, U1.7 (GPIO4)
GPIO17: GPIO17.I/O, U1.11 (GPIO17)
GPIO18: GPIO18.I/O, U1.12 (GPIO18)
GPIO22: GPIO22.I/O, U1.15 (GPIO22)
GPIO23: GPIO23.I/O, U1.16 (GPIO23)
GPIO24: GPIO24.I/O, U1.18 (GPIO24)
GPIO25: GPIO25.I/O, U1.22 (GPIO25)
GPIO27: GPIO27.I/O, U1.13 (GPIO27)
MISO: IC1.12 (DOUT), U1.21 (MISO)
MOSI: IC1.11 (DIN), U1.19 (MOSI)
RX: SERIAL.RX, U1.10 (RX)
SCL: I2C1.SCL, I2C2.SCL, I2C3.SCL, U1.5 (SCL)
SCLK: IC1.13 (CLK), U1.23 (SCLK)
SDA: I2C1.SDA, I2C2.SDA, I2C3.SDA, U1.3 (SDA)
TX: SERIAL.TX, U1.8 (TX)

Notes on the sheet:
1.0.5
GPIO (3pin Top 2mm pitch) x8
I2C(4pin Side 2mm pitch) x
Analog Input (3pin Top 2mm pitch) x8
Serial (4pin Side 2mm pitch)
